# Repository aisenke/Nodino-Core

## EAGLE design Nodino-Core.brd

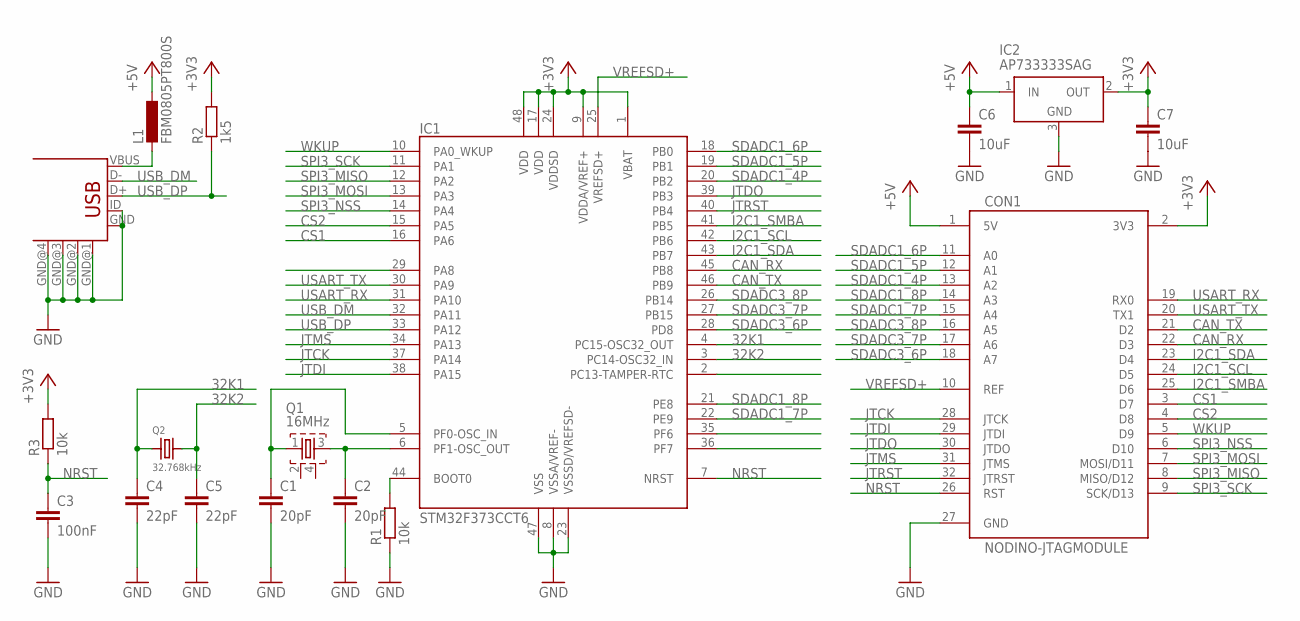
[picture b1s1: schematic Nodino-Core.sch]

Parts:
C1, C2: 20pF; C0603K
C3: 100nF; C0603K
C4, C5: 22pF; C0603K
C6, C7: 10uF; C0603K
CON1: NODINO-JTAGMODULE; NODINO-JTAG-MOD
CON2: USB-OTG_SHIELD; USB-UAB-S1
IC1: STM32F373CCT6; LQFP48
IC2: AP733333SAG; SOT23
L1: FBM0805PT800S; L0805
Q1: 16MHz; FA-20H
Q2: 32.768kHz; ABS07
R1, R3: 10k; R0603K
R2: 1k5; R0603K

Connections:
32K1: C4.1, IC1.4 (PC15-OSC32_OUT), Q2.1
32K2: C5.1, IC1.3 (PC14-OSC32_IN), Q2.2
+3V3: C7.1, CON1.2 (3V3), IC1.1 (VBAT), IC1.9 (VDDA/VREF+), IC1.17 (VDD), IC1.24 (VDDSD), IC1.48 (VDD), IC2.2 (OUT), R2.2, R3.2
+5V: C6.1, CON1.1 (5V), IC2.1 (IN), L1.1
CAN_RX: CON1.22 (D3), IC1.45 (PB8)
CAN_TX: CON1.21 (D2), IC1.46 (PB9)
CS1: CON1.3 (D7), IC1.16 (PA6)
CS2: CON1.4 (D8), IC1.15 (PA5)
GND: C1.2, C2.2, C3.2, C4.2, C5.2, C6.2, C7.2, CON1.27 (GND), CON2.GND, CON2.GND@1 (GND), CON2.GND@2 (GND), CON2.GND@3 (GND), CON2.GND@4 (GND), CON2.ID, IC1.8 (VSSA/VREF-), IC1.23 (VSSSD/VREFSD-), IC1.47 (VSS), IC2.3 (GND), R1.1
I2C1_SCL: CON1.24 (D5), IC1.42 (PB6)
I2C1_SDA: CON1.23 (D4), IC1.43 (PB7)
I2C1_SMBA: CON1.25 (D6), IC1.41 (PB5)
JTCK: CON1.28 (JTCK), IC1.37 (PA14)
JTDI: CON1.29 (JTDI), IC1.38 (PA15)
JTDO: CON1.30 (JTDO), IC1.39 (PB3)
JTMS: CON1.31 (JTMS), IC1.34 (PA13)
JTRST: CON1.32 (JTRST), IC1.40 (PB4)
unnamed: CON2.VBUS, L1.2
unnamed: IC1.44 (BOOT0), R1.2
unnamed: C2.1, IC1.6 (PF1-OSC_OUT), Q1.3
unnamed: C1.1, IC1.5 (PF0-OSC_IN), Q1.1
NRST: C3.1, CON1.26 (RST), IC1.7 (NRST), R3.1
PA8: IC1.29 (PA8)
PC13: IC1.2 (PC13-TAMPER-RTC)
PF6: IC1.35 (PF6)
PF7: IC1.36 (PF7)
SDADC1_4P: CON1.13 (A2), IC1.20 (PB2)
SDADC1_5P: CON1.12 (A1), IC1.19 (PB1)
SDADC1_6P: CON1.11 (A0), IC1.18 (PB0)
SDADC1_7P: CON1.15 (A4), IC1.22 (PE9)
SDADC1_8P: CON1.14 (A3), IC1.21 (PE8)
SDADC3_6P: CON1.18 (A7), IC1.28 (PD8)
SDADC3_7P: CON1.17 (A6), IC1.27 (PB15)
SDADC3_8P: CON1.16 (A5), IC1.26 (PB14)
SPI3_MISO: CON1.8 (MISO/D12), IC1.12 (PA2)
SPI3_MOSI: CON1.7 (MOSI/D11), IC1.13 (PA3)
SPI3_NSS: CON1.6 (D10), IC1.14 (PA4)
SPI3_SCK: CON1.9 (SCK/D13), IC1.11 (PA1)
USART_RX: CON1.19 (RX0), IC1.31 (PA10)
USART_TX: CON1.20 (TX1), IC1.30 (PA9)
USB_DM: CON2.D-, IC1.32 (PA11)
USB_DP: CON2.D+, IC1.33 (PA12), R2.1
VREFSD+: CON1.10 (REF), IC1.25 (VREFSD+)
WKUP: CON1.5 (D9), IC1.10 (PA0_WKUP)

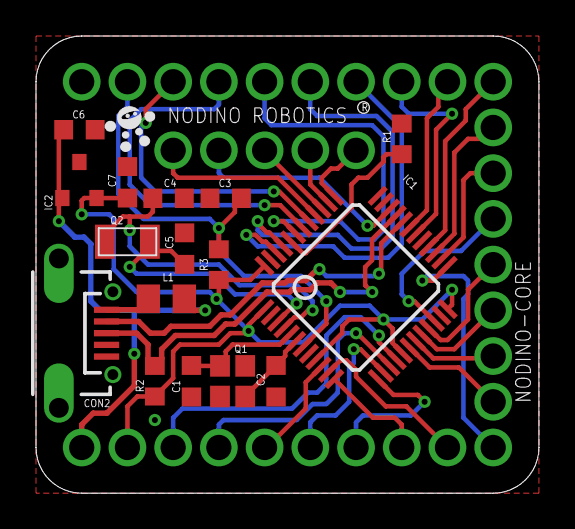
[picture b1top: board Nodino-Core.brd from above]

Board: 2 copper layers, 27.9 x 25.4 mm, 17 parts (0 on the bottom side), 40 nets.

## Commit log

2014-03-23 Initial commit
    Initial commit of Nodino-Core
2014-03-23 Renaming CM4 to Core
2014-03-23 Name and value renumbering
2014-03-26 Added board name
2014-03-26 Added basic pin assignment
2014-03-27 added ground plane filling on bottom layer
2014-03-27 added filter capacitors
